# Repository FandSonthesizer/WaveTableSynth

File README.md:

# WaveTableSynth
This is a wavetable synth based on our Essential Shield project. It got midi, multiple voices, fm voices, ADSR and so on.
Based on the STM32 'Blue Pill' one can build this nice little gadget for less than 50€!

We added a 24dB VCF based on a Ray Wilson design (MusicFromOuterSpace) and got really good results. The VCF project is also included here.

Have fun building this project and even more fun to putting it to good use. :-)

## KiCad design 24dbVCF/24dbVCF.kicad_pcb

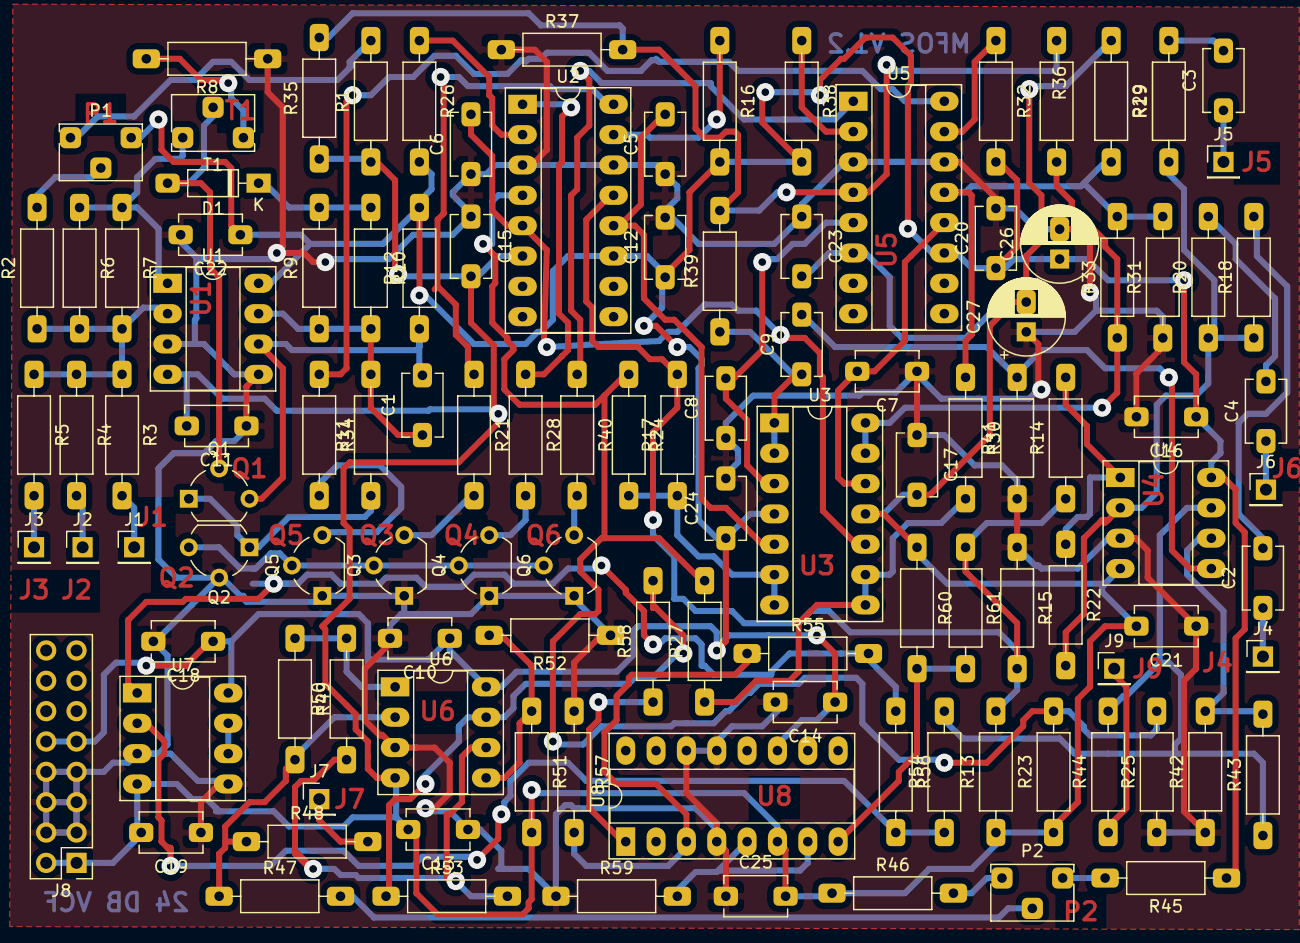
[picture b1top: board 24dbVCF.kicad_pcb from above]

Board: 2 copper layers, 115 parts (0 on the bottom side), 69 nets.

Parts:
C1, C5, C6, C7, C8: 100p; Kondensator_Keramik
C2, C3, C4, C9, C10, C11, C12, C13, C14, C15, C16, C17, C18, C19, C20, C21, C22, C23, C24, C25: 100n; Kondensator_Keramik
C26, C27: 10u; Elko_D6.3mm_P2.50mm
D1: 1N4148; D_DO-35_SOD27_P7.62mm_Horizontal
J1: CV1; Stift
J2: CV2; Stift
J3: CV3; Stift
J4: Audio1; Stift
J5, J6: Audio2; Stift
J7: Res; Stift
J8: Conn_02x08_Odd_Even; PinHeader_2x08_P2.54mm_Vertical
J9: Out; Stift
P1, P2: 100k; Trimmer_Vertical
Q1, Q2: 2N3904; TO-92_Wide
Q3, Q4, Q5, Q6: 2N3906; TO-92_Wide
R1: 75k; Widerstand_liegend
R2, R3, R4, R5, R14, R17, R24, R27, R30, R33, R36, R39, R42, R43, R47, R48, R50, R51, R53: 100k; Widerstand_liegend
R6: 7.5k; Widerstand_liegend
R7, R44: 2k; Widerstand_liegend
R8: 475; Widerstand_liegend
R9: 47k; Widerstand_liegend
R10: 68k; Widerstand_liegend
R11, R21, R28, R34, R40: 10k; Widerstand_liegend
R12: 1M; Widerstand_liegend
R13, R23: 39k; Widerstand_liegend
R15, R25, R31, R37: 100; Widerstand_liegend
R16, R26, R32, R38: 20k; Widerstand_liegend
R18, R19, R20, R55: 200k; Widerstand_liegend
R22: 300k; Widerstand_liegend
R29, R35: 43k; Widerstand_liegend
R41: 4.7m; Widerstand_liegend
R45, R46: 49.9k; Widerstand_liegend
R49, R56: 120k; Widerstand_liegend
R52, R54, R58, R59: 30k; Widerstand_liegend
R57: 1k; Widerstand_liegend
R60: 4.7k; Widerstand_liegend
R61: 150k; Widerstand_liegend
T1: 100; Trimmer_Vertical
U1, U4, U6, U7: TL072; DIP-8_W7.62mm_Socket_LongPads
U2, U5, U8: LM13700; DIP-16_W7.62mm_Socket_LongPads
U3: TL074; DIP-14_W7.62mm_Socket_LongPads

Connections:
+12V: C10.1, C12.1, C14.1, C16.1, C18.1, C20.1, C22.1, C24.1, C26.1, J8.9, J8.10, P1.1, R12.2, R16.2, R26.2, R32.2, R38.2, R45.1, U1.8, U2.11, U3.4, U4.8, U5.11, U6.8, U7.8, U8.11
-12V: C11.2, C13.2, C15.2, C17.2, C19.2, C21.2, C23.2, C25.2, C27.2, J8.1, J8.2, R1.1, R13.1, R23.1, R29.1, R35.1, R46.1, R51.2, R60.1, U1.4, U2.6, U3.11, U4.4, U5.6, U6.4, U7.4, U8.6
GND: C5.1, C6.1, C7.1, C8.1, C10.2, C11.1, C12.2, C13.1, C14.2, C15.1, C16.2, C17.1, C18.2, C19.1, C20.2, C21.1, C22.2, C23.1, C24.2, C25.1, C26.2, C27.1, J8.3, J8.4, J8.5, J8.6, J8.7, J8.8, Q2.2, Q3.1, Q4.1, Q5.1, Q6.1, R8.1, R15.1, R25.1, R31.1, R37.1, R41.1, R42.1, R52.1, R57.1, R59.1, U1.3, U1.5, U2.3, U2.14, U4.3, U5.3, U5.14, U6.3, U7.3, U7.5, U8.4, U8.13, U8.14
unnamed: C1.1, R9.1, R10.2, R11.2, U1.7
unnamed: C1.2, Q1.3, R12.1, U1.6
unnamed: C2.1, J4.1
unnamed: C2.2, R18.2
unnamed: C3.1, J5.1
unnamed: C3.2, R19.2
unnamed: C4.1, J6.1
unnamed: C4.2, R20.2
unnamed: C5.2, U2.12, U3.5
unnamed: C6.2, U2.5, U3.10
unnamed: C7.2, U3.12, U5.12
unnamed: C8.2, U3.3, U5.5
unnamed: C9.1, R39.1, U3.1, U3.2
unnamed: C9.2, R41.2, U4.5
unnamed: D1.1, R9.2, R10.1
unnamed: D1.2, Q1.2, T1.2
unnamed: J1.1, R3.2
unnamed: J2.1, R4.2
unnamed: J3.1, R5.2
unnamed: J7.1, R48.2
unnamed: J9.1, R44.1
unnamed: P1.2, R2.2
unnamed: P1.3, R1.2
unnamed: P2.1, R45.2
unnamed: P2.2, R47.2
unnamed: P2.3, R46.2
unnamed: Q1.1, Q2.1, R11.1
unnamed: Q2.3, Q3.2, Q4.2, Q5.2, Q6.2
unnamed: Q3.3, R21.2
unnamed: Q4.3, R28.2
unnamed: Q5.3, R34.2
unnamed: Q6.3, R40.2
unnamed: R2.1, R3.1, R4.1, R5.1, R6.2, R7.2, U1.2
unnamed: R6.1, R7.1, T1.1, U1.1
unnamed: R8.2, T1.3
unnamed: R14.2, R22.1, U4.1
unnamed: R16.1, U2.15
unnamed: R17.1, R24.2, U3.6, U3.7
unnamed: R18.1, R19.1, R20.1, R22.2, U4.2
unnamed: R21.1, U2.16
unnamed: R23.2, R24.1, R25.2, R27.2, U2.4
unnamed: R26.1, U2.2
unnamed: R27.1, R30.2, U3.8, U3.9
unnamed: R28.1, U2.1
unnamed: R29.2, R30.1, R31.2, R33.2, U5.13
unnamed: R32.1, U5.15
unnamed: R33.1, R36.2, U3.13, U3.14
unnamed: R34.1, U5.16
unnamed: R35.2, R36.1, R37.2, R39.2, U5.4
unnamed: R38.1, U5.2
unnamed: R40.1, U5.1
unnamed: R42.2, R43.2, U4.6
unnamed: R47.1, R48.1, R49.2, U6.2
unnamed: R49.1, R50.2, U6.1
unnamed: R50.1, R53.2, U6.6
unnamed: R51.1, R52.2, U6.5
unnamed: R53.1, R58.2, U6.7
unnamed: R54.1, R56.2, U7.2
unnamed: R55.1, R57.2, U8.3
unnamed: R55.2, R56.1, U7.1
unnamed: R58.1, U8.1
unnamed: R59.2, U8.5, U8.7
unnamed: R60.2, R61.2, U8.8
unnamed: U7.6, U7.7
RA: R43.1, R44.2, R54.2, U4.7
RB: R13.2, R14.1, R15.2, R17.2, R61.1, U2.13

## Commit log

2020-06-23 Delete 24dbVCF.pro
    Wrong file upload
2020-06-24 Correction of right shift operation to correspond division by 4 in Synth Audio Mixer part for total sum of signals
